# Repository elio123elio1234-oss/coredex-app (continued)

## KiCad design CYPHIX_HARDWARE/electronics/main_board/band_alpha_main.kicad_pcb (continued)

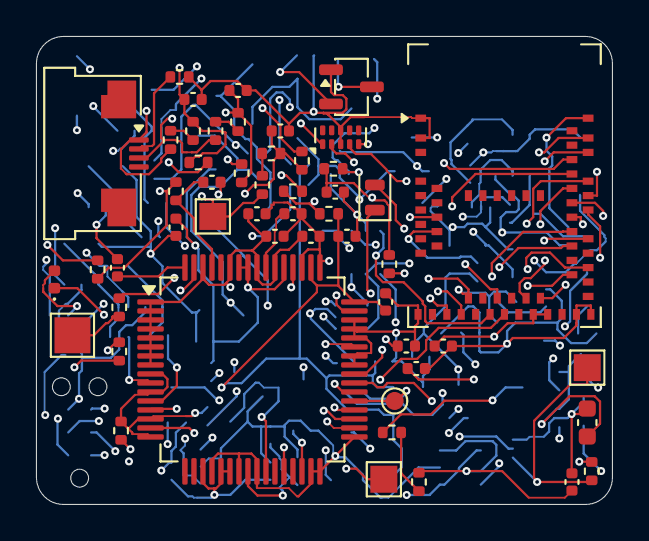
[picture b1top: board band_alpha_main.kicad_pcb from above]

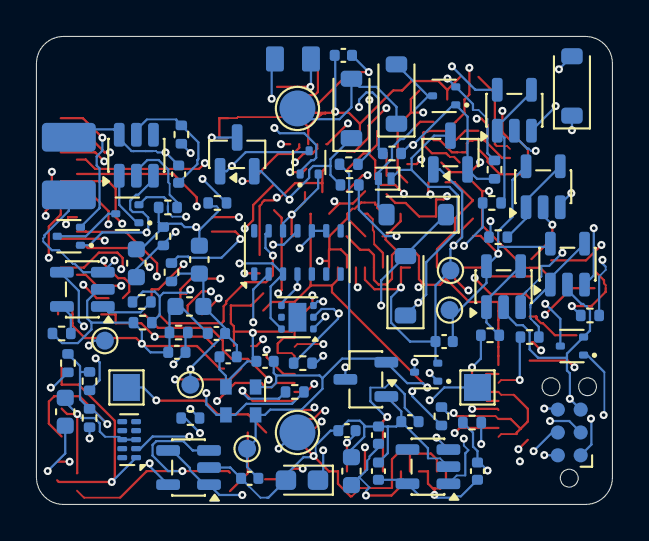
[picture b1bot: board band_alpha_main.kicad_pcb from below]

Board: 6 copper layers, 32.0 x 26.0 mm, 136 parts (84 on the bottom side), 89 nets.

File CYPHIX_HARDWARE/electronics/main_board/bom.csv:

qty,value,footprint,fit,references
1,LiPo 401225 ~100 mAh (no own PCM),band_alpha:Cell_Tabs_2x,fit,BT1
8,100n,Capacitor_SMD:C_0402_1005Metric,fit,C1 C9 C16 C18 C20 C22 C24 C31
5,1n C0G,Capacitor_SMD:C_0402_1005Metric,fit,C10 C11 C12 C13 C14
4,4u7,Capacitor_SMD:C_0603_1608Metric,fit,C2 C3 C4 C30
1,10u,Capacitor_SMD:C_0603_1608Metric,fit,C23
1,1n,Capacitor_SMD:C_0402_1005Metric,fit,C28
1,1.5n,Capacitor_SMD:C_0402_1005Metric,fit,C29
2,12p C0G,Capacitor_SMD:C_0402_1005Metric,fit,C32 C33
11,1u,Capacitor_SMD:C_0402_1005Metric,fit,C5 C6 C7 C8 C15 C17 C19 C21 C25 C26 C27
1,22u tantalum,Capacitor_Tantalum_SMD:CP_EIA-2012-12_Kemet-R,fit,C90
5,MBR0520,Diode_SMD:D_SOD-123,fit,D1 D2 D3 D4 D7
1,PESD5V0S1UL,Diode_SMD:D_SOD-882,fit,D5
1,white 0402,LED_SMD:LED_0402_1005Metric,fit,D6
1,"FPC 4p 0.5 mm, Amphenol F32Q (strap flex)",Connector_FFC-FPC:Amphenol_F32Q-1A7x1-11004_1x04-1MP_P0.5mm_Horizontal,fit,J1
1,coin motor 8 mm,band_alpha:Motor_Pads_2x,fit,M1
6,DMG1012T,Package_TO_SOT_SMD:SOT-523,fit,Q1 Q2 Q4 Q5 Q6 Q7
1,AO3401A,Package_TO_SOT_SMD:SOT-23,fit,Q3
1,100,Resistor_SMD:R_0402_1005Metric,fit,R1
2,10M,Resistor_SMD:R_0402_1005Metric,fit,R12 R13
10,47.5k 0.1%,Resistor_SMD:R_0402_1005Metric,fit,R14 R15 R18 R19 R22 R23 R26 R27 R30 R31
7,0,Resistor_SMD:R_0402_1005Metric,fit,R16 R20 R24 R28 R32 R36 R38
3,1k,Resistor_SMD:R_0402_1005Metric,fit,R2 R42 R44
4,1M,Resistor_SMD:R_0402_1005Metric,fit,R3 R4 R5 R37
1,330,Resistor_SMD:R_0402_1005Metric,fit,R41
1,20k,Resistor_SMD:R_0402_1005Metric,fit,R6
6,100k,Resistor_SMD:R_0402_1005Metric,fit,R7 R9 R11 R34 R35 R43
2,200k,Resistor_SMD:R_0402_1005Metric,fit,R8 R10
1,spring contact LA pad 1,TestPoint:TestPoint_Pad_1.5x1.5mm,fit,SC1
1,spring contact LA pad 2,TestPoint:TestPoint_Pad_1.5x1.5mm,fit,SC2
1,spring contact LL1,TestPoint:TestPoint_Pad_1.5x1.5mm,fit,SC3
1,spring contact LL2,TestPoint:TestPoint_Pad_1.5x1.5mm,fit,SC4
1,spring contact RLD,TestPoint:TestPoint_Pad_1.5x1.5mm,fit,SC5
1,charge contact A,TestPoint:TestPoint_Pad_D2.0mm,fit,TP1
1,charge contact B,TestPoint:TestPoint_Pad_D2.0mm,fit,TP2
1,DW01A,Package_TO_SOT_SMD:SOT-23-6,fit,U1
2,TPD4E02B04DQA,Package_SON:USON-10_2.5x1.0mm_P0.5mm,fit,U10 U11
1,TPS3839K33DBZR,Package_TO_SOT_SMD:SOT-23,fit,U2
1,MCP73831-2-OT,Package_TO_SOT_SMD:SOT-23-5,fit,U3
1,XC6206P302MR,Package_TO_SOT_SMD:SOT-23-3,fit,U4
1,LP5907MFX-3.0,Package_TO_SOT_SMD:SOT-23-5,fit,U5
1,ADS1294IPAG,Package_QFP:TQFP-64_10x10mm_P0.5mm,fit,U6
1,MDBT50Q-1MV2,RF_Module:Raytac_MDBT50Q,fit,U7
1,"32.768 kHz, CL 9 pF",Crystal:Crystal_SMD_2012-2Pin_2.0x1.2mm,fit,Y1
1,100n,Capacitor_SMD:C_0402_1005Metric,DNP,C34
1,10u,Capacitor_SMD:C_0603_1608Metric,DNP,C35
1,1u,Capacitor_SMD:C_0402_1005Metric,DNP,C36
7,0,Resistor_SMD:R_0402_1005Metric,DNP,R17 R21 R25 R29 R33 R39 R40
2,4.7k,Resistor_SMD:R_0402_1005Metric,DNP,R45 R46
2,10k,Resistor_SMD:R_0402_1005Metric,DNP,R47 R48
1,XC6206P182MR,Package_TO_SOT_SMD:SOT-23-3,DNP,U12
5,AD8603,Package_TO_SOT_SMD:TSOT-23-5,DNP,U20 U21 U22 U23 U24
1,TMP117AIDRVR,Package_SON:WSON-6-1EP_2x2mm_P0.65mm_EP1x1.6mm,DNP,U8
1,MAX30102,OptoDevice:Maxim_OLGA-14_3.3x5.6mm_P0.8mm,DNP,U9
1,ASDMB-2.048MHz,Oscillator:Oscillator_SMD_Abracon_ASDMB-4Pin_2.5x2.0mm,DNP,Y2

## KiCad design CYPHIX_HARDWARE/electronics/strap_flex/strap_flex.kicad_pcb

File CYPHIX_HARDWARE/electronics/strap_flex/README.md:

# Strap flex, rev 0.1

The flexible circuit moulded inside the FKM strap. It carries RA1 and RA2 from the two finger plates on top
of the strap into the island, to J1 on the main board.

**Status:** drawn and checked by KiCad's DRC: 0 errors, 0 unconnected. One warning stays visible: the guard
trace ends open at its far end, which is how a guard is meant to be. Not reviewed, not ordered.

| | |
|---|---|
| Files | `strap_flex.kicad_pcb`, from `make_flex.py` (KiCad's Python). Picture: `pics/flex_top3d.png` |
| Build | Single-sided: 18 µm rolled-annealed copper on 25 µm polyimide, coverlay both sides, about 0.11 mm thick. ENIG on the exposed pads and fingers. |
| Size (flat) | 61.7 mm long. 13.4 mm wide in the strap, which is 24 mm wide. 2.5 mm tail. |
| Lanes | RA1 at y +3.4 mm, guard at 0, RA2 at −3.4 mm. 0.3 mm wide in the strap, 0.2 mm in the tail. Each RA plate on its own trace, the guard between them (DESIGN_INTENT §1, the owner's rule). |
| Post pads | 4 mm round pads, exposed. RA1 at 34.5 mm and RA2 at 49.1 mm from the island's end, measured along the strap's mid-thickness on the design wrist (`mechanical/band_id.py` v3.2: posts at s = −55 / −69, y = ±3.4). The plate's steel post presses onto its pad. |
| Interlock | 20 holes, 1.1 mm, down both edges every 4 mm. The FKM flows through them and locks the flex in place. None within 3.5 mm of a post pad. |
| Tail | 4 fingers, 0.5 mm pitch, 3 mm long, pulled back 0.3 mm from the tip. 0.2 mm PI stiffener, 0.3 mm total, for the ZIF connector J1 (Amphenol F32Q). Pin 1 RA1, 2 guard, 3 RA2, 4 unused. Net names as on the main board. |

**To confirm before ordering:**
- The FPC tail width, finger length and contact side against the F32Q-1A7x1-11004 drawing (top or bottom
  contact decides which way the fingers face).
- The exact post positions once the strap length per size is decided. Three strap lengths are still open.
- Bend life of the tail where it rises from mid-strap to the board, about 2.3 mm in height. The board
  house's flex rules apply.

<!-- v0.1.0 — strap flex rev 0.1: what it is, build, geometry from the 3D model, tail for J1, items to confirm -->

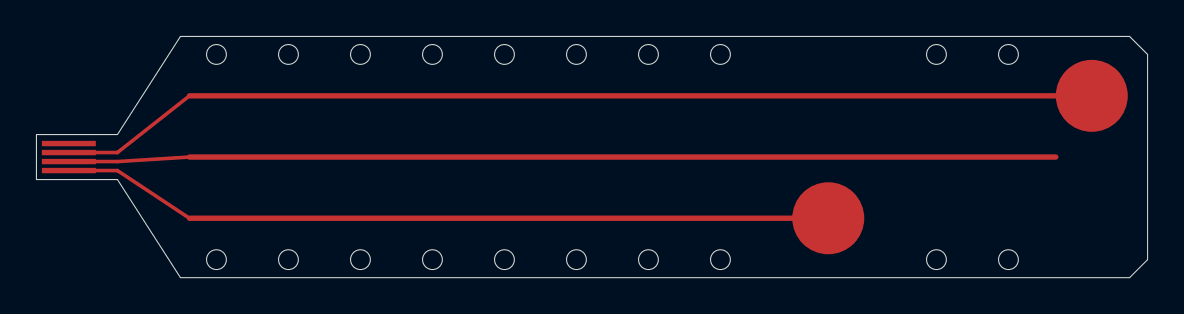
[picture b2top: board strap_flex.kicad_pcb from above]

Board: 2 copper layers, 61.7 x 13.4 mm, 23 parts (0 on the bottom side), 2 nets.

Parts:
H1, H2, H3, H4, H5, H6, H7, H8, H9, H10, H11, H12, H13, H14, H15, H16, H17, H18, H19, H20: interlock hole
P1: FPC tail 4 x 0.5 mm
P_RA1: RA1 post pad
P_RA2: RA2 post pad

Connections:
/RA1_PAD: P1.1, P_RA1.1
/RA2_PAD: P1.3, P_RA2.1

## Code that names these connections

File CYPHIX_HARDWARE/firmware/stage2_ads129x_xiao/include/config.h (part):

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  #error "Seeed XIAO pin macros not found - check `board = xiaoble(sense)_adafruit` in platformio.ini"
#endif

#define PIN_ADS_PWDN    D0    // pad 0  -> ADS PWDN   (active low: LOW = powered down)
#define PIN_ADS_RESET   D1    // pad 1  -> ADS RESET  (active low)
#define PIN_ADS_START   D2    // pad 2  -> ADS START  (HIGH = convert)
#define PIN_ADS_DRDY    D3    // pad 3  <- ADS DRDY   (falls when a conversion is ready)
#define PIN_ADS_CS      D7    // pad 7  -> ADS CS     (active low)
// pad 8  -> ADS SCLK      pad 9  <- ADS DOUT      pad 10 -> ADS DIN
// These three are fixed by the board variant; the checks below stop the build
// if a different core ever moves them.
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  { 4, +1 },   // logical CH3 = LL1 - LA  : LL1 on IN4P (J1-1), LA bus on IN4N
  { 5, +1 },   // logical CH4 = LL2 - LA  : LL2 on IN5P (J1-2), LA bus on IN5N
};
// On TI's board GPIO1/GPIO2 go to open header pins and GPIO3/GPIO4 to an unfitted
// header. The datasheet says not to leave GPIO pins floating (section 9.3.2.1),
// so the four pins become outputs driving low.
#define ADS_GPIO_ALL_OUTPUTS  1
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// ------------------------------------------------------------
// 6. Power-up timing (section 11.1, Table 38, Figure 93)
// ------------------------------------------------------------
#define ADS_POWER_UP_MS       1000   // >= tPOR (2^18 tCLK = 128 ms) AND until VCAP1 >= 1.1 V
#define ADS_REF_SETTLE_MS     150    // internal reference start-up time (Electrical Characteristics)

// ------------------------------------------------------------
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
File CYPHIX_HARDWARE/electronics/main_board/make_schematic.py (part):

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place("Diode:MBR0520", "D2", "MBR0520", 205, 55, {"2": "CHG_B", "1": "BR_P"})
place("Diode:MBR0520", "D3", "MBR0520", 205, 70, {"2": "BR_N", "1": "CHG_A"})
place("Diode:MBR0520", "D4", "MBR0520", 205, 85, {"2": "BR_N", "1": "CHG_B"})
place("Diode:PESD5V0S1UL", "D5", "PESD5V0S1UL", 230, 62, {"1": "BR_P", "2": "BR_N"}, rot=90,
      note="ESD across the bridge output; leaks only inside the bridge loop, never to circuit ground")
place("Power_Supervisor:TPS3839DBZ", "U2", "TPS3839K33DBZR", 255, 45, {"3": "BR_P", "1": GND, "2": "CHG_PG"},
      note="VIT ~3.08 V (K33, to confirm); ~150 nA from BR_P is the only DC path from a contact when not charging")
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      note="4.20 V linear charger; IREG = 1000 V / RPROG")
R("20k", "CHG_PROG", GND, 390, 70, rot=0, note="RPROG: 1000 V / 20 kOhm = 50 mA (0.5 C)")
C("4u7", VBAT, GND, 400, 50, fp=C0603)
R("100k", "CHG_STAT_RAW", "CHG_STAT", 405, 80, note="STAT swings to VCHG (4.4 V): divider to the 3.0 V GPIO")
R("200k", "CHG_STAT", GND, 420, 90, rot=0)
R("100k", "CHG_PG", "VBUS_DET", 275, 90, note="CHG_PG ~4.4 V when charging -> 2.9 V at the GPIO")
R("200k", "VBUS_DET", GND, 285, 100, rot=0)
pwr_flag("BR_P", 220, 30)
pwr_flag("VCHG", 330, 38)
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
